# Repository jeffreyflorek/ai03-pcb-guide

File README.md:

This is the repository I'm using for my run through of ai03's [PCB Guide](https://wiki.ai03.com/books/pcb-design/chapter/pcb-designer-guide).

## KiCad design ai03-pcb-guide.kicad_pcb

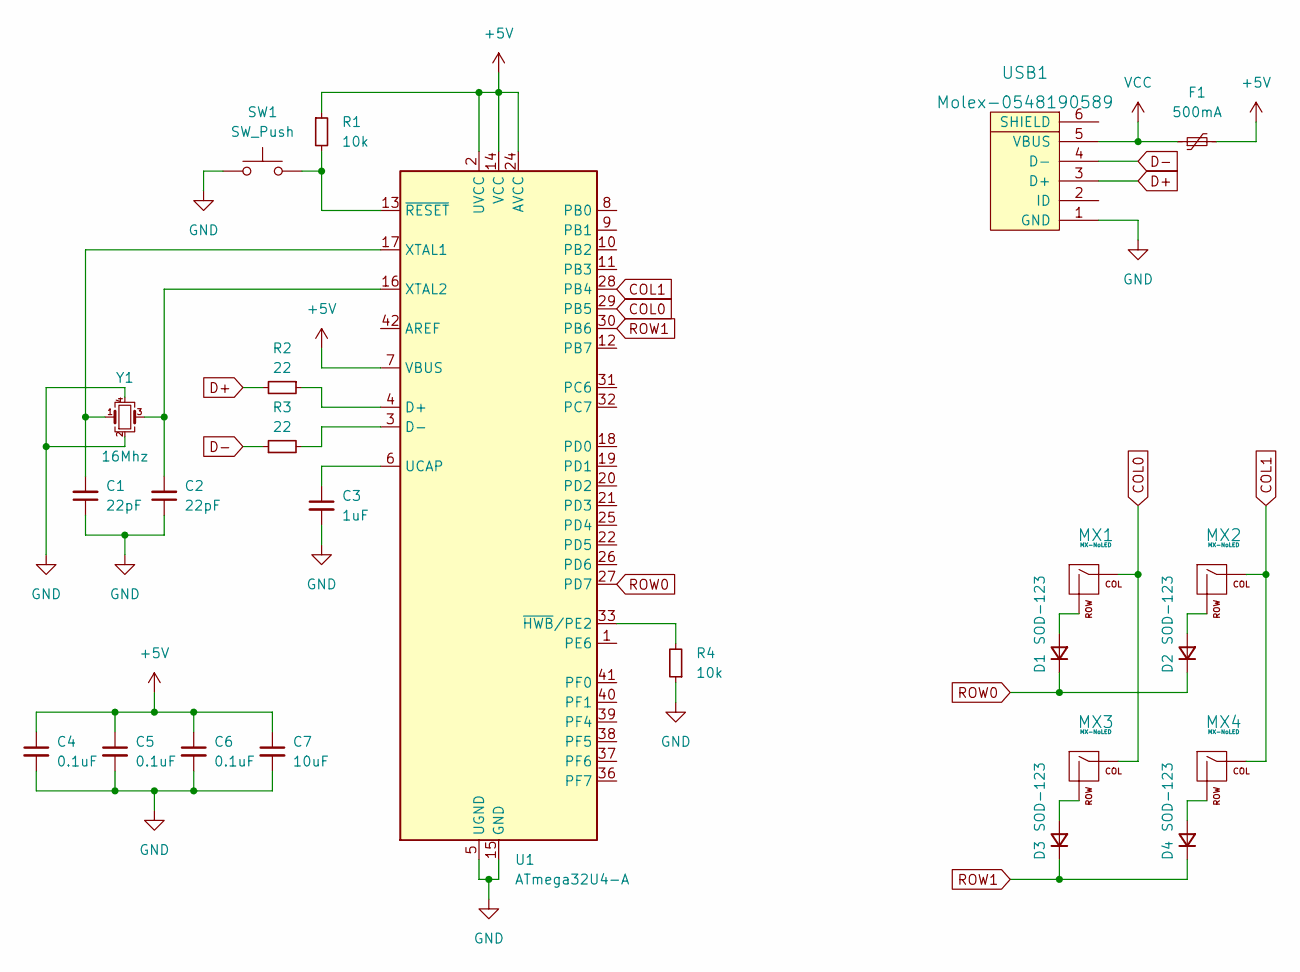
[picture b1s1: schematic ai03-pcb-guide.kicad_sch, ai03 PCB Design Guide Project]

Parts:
C1, C2: 22pF; C_0805_2012Metric
C3: 1uF; C_0805_2012Metric
C4, C5, C6: 0.1uF; C_0805_2012Metric
C7: 10uF; C_0805_2012Metric
D1, D2, D3, D4: SOD-123; D_SOD-123
F1: 500mA; Fuse_1206_3216Metric
MX1, MX2, MX3, MX4: MX-NoLED; MX-1U-NoLED
R1, R4: 10k; R_0805_2012Metric
R2, R3: 22; R_0805_2012Metric
SW1: SW_Push; SKQG-1155865
U1: ATmega32U4-A; TQFP-44_10x10mm_P0.8mm
USB1: Molex-0548190589
Y1: 16Mhz; Crystal_SMD_3225-4Pin_3.2x2.5mm

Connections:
+5V: C4.1, C5.1, C6.1, C7.1, F1.2, R1.1, U1.2 (UVCC), U1.7 (VBUS), U1.14 (VCC), U1.24 (AVCC), U1.34 (VCC), U1.44 (AVCC)
COL0: MX1.1 (COL), MX3.1 (COL), U1.29 (PB5)
COL1: MX2.1 (COL), MX4.1 (COL), U1.28 (PB4)
D+: R2.2, USB1.3 (D+)
D-: R3.1, USB1.4 (D-)
GND: C1.1, C2.1, C3.2, C4.2, C5.2, C6.2, C7.2, R4.1, SW1.1, U1.5 (UGND), U1.15 (GND), U1.23 (GND), U1.35 (GND), U1.43 (GND), USB1.1 (GND), Y1.2, Y1.4
unnamed: C1.2, U1.17 (XTAL1), Y1.1
unnamed: C2.2, U1.16 (XTAL2), Y1.3
unnamed: C3.1, U1.6 (UCAP)
unnamed: D1.2 (A), MX1.2 (ROW)
unnamed: D2.2 (A), MX2.2 (ROW)
unnamed: D3.2 (A), MX3.2 (ROW)
unnamed: D4.2 (A), MX4.2 (ROW)
unnamed: R1.2, SW1.2, U1.13 (~RESET)
unnamed: R2.1, U1.4 (D+)
unnamed: R3.2, U1.3 (D-)
unnamed: R4.2, U1.33 (~HWB/PE2)
ROW0: D1.1 (K), D2.1 (K), U1.27 (PD7)
ROW1: D3.1 (K), D4.1 (K), U1.30 (PB6)
VCC: F1.1, USB1.5 (VBUS)

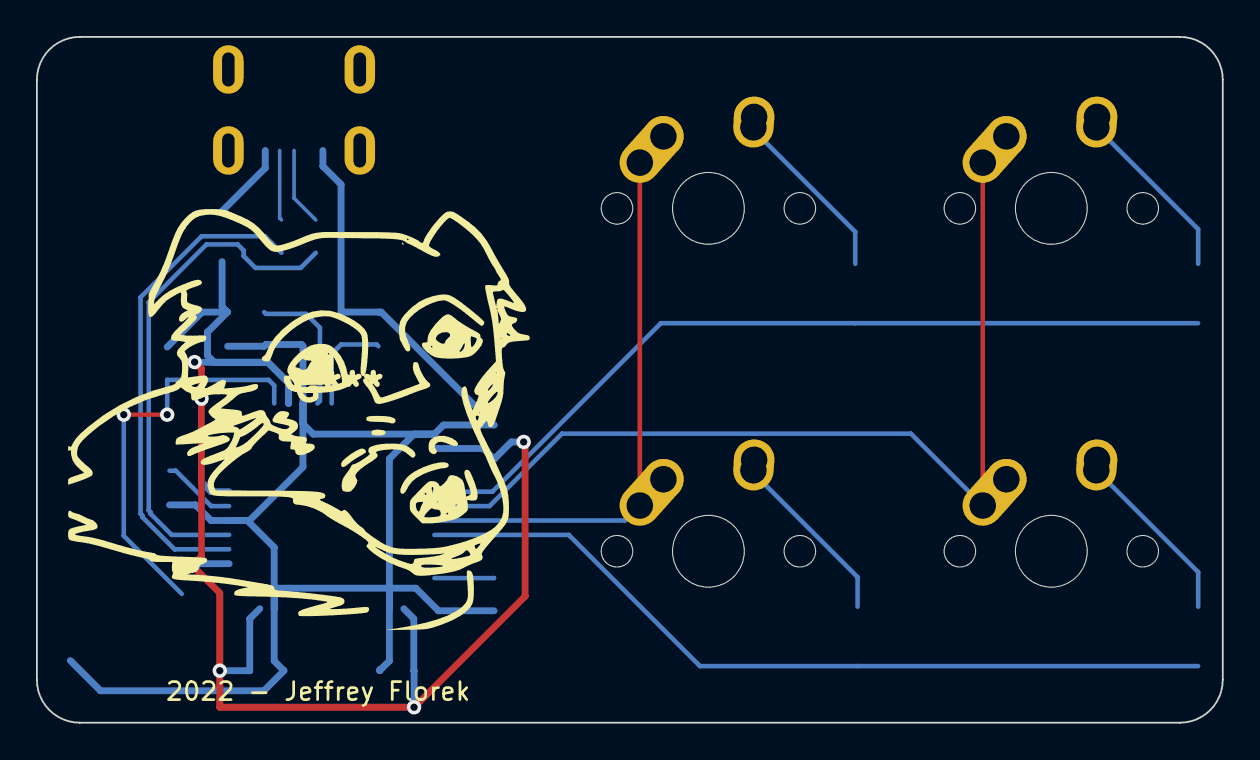
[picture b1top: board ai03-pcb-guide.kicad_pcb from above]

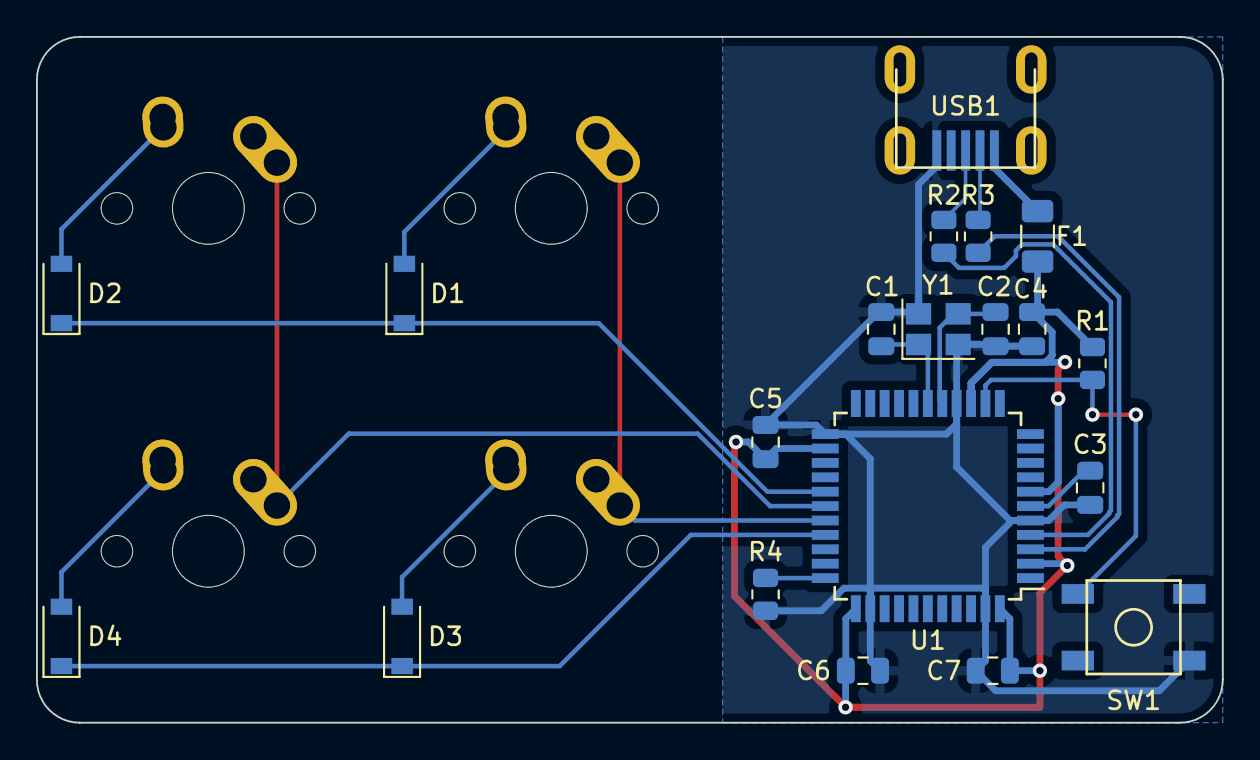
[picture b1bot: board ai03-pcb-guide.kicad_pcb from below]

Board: 2 copper layers, 65.9 x 38.1 mm, 24 parts (20 on the bottom side), 20 nets.

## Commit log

2022-12-17 Actually added text to README...
2022-12-17 Create LICENSE
2022-12-17 Create KiCad project.
2022-12-17 Add KiCad libraries as submodules.
2022-12-17 Cleanup.
2022-12-17 Add custom libraries to KiCad project.
2022-12-18 Add MCU and supporting components to schematic.
    Added the following to the schematic:
    - ATmega32u4 microcontroller,
    - 16 MHz crystal,
    - Reset switch with pullup resistor, and
    - Various bypass capacitors.
2022-12-18 Annotate schematic and assign footprints.
2022-12-18 Create and route PCB.
2022-12-18 Reroute PCB and add ground fill.
2022-12-18 Add silly line art of my dog to the PCB.
